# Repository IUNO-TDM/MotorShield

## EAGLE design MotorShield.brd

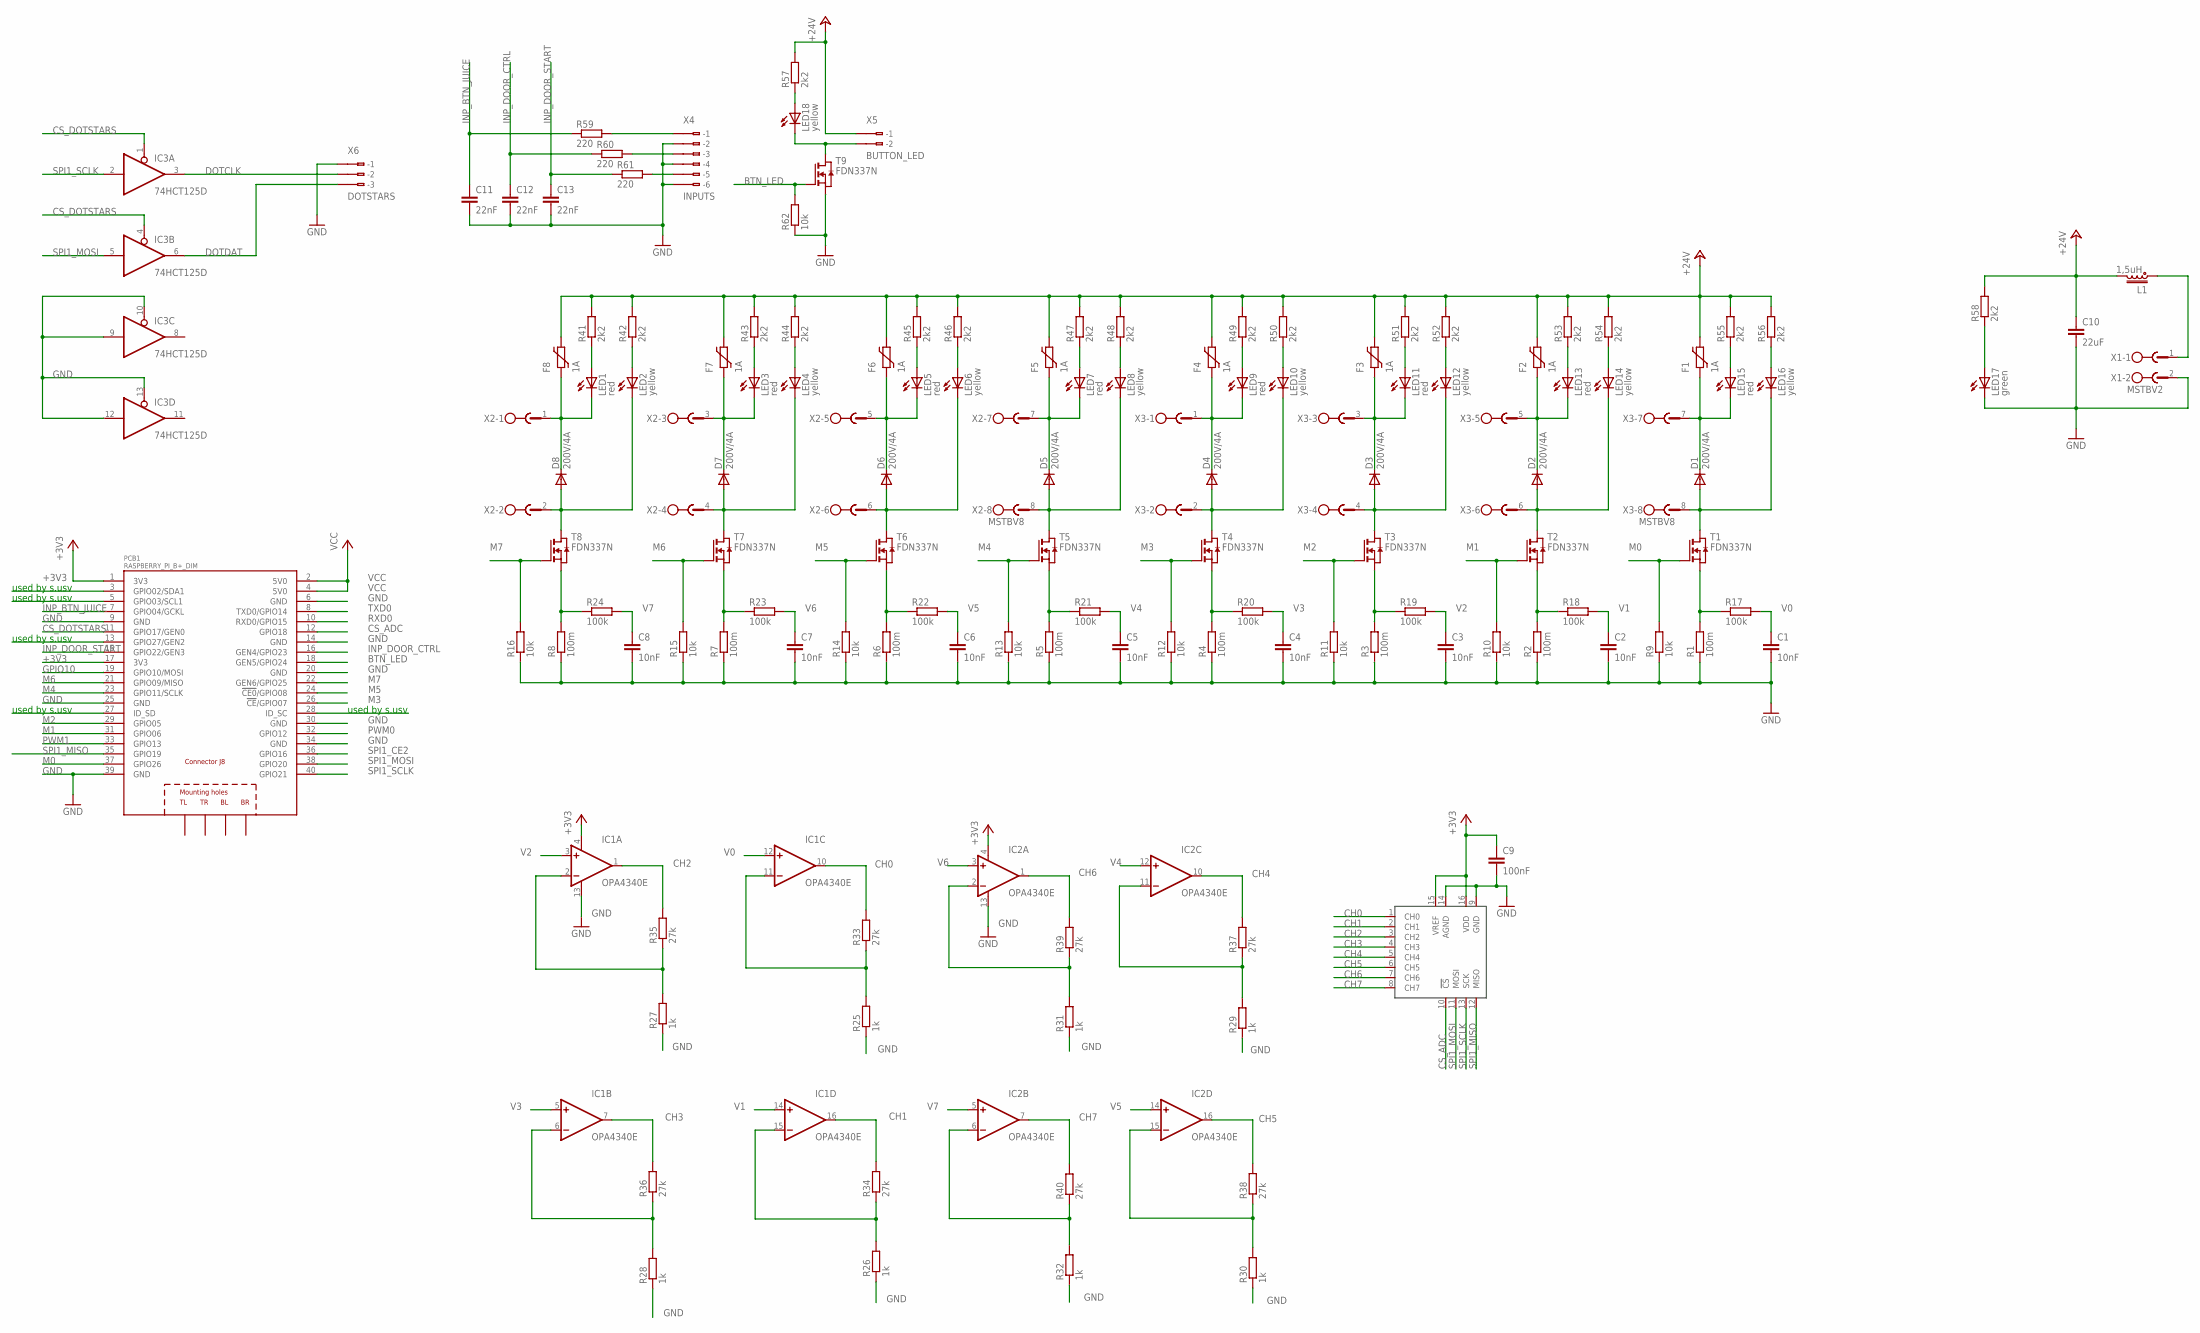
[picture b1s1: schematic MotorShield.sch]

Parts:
C1, C2, C3, C4, C5, C6, C7, C8: 10nF; C0805
C9: 100nF; C0805
C10: 22uF; C1812
C11, C12, C13: 22nF; C0805K
D1, D2, D3, D4, D5, D6, D7, D8: 200V/4A; DO214AA
F1, F2, F3, F4, F5, F6, F7, F8: 1A; 1812L
IC1, IC2: OPA4340E; SSOP16BU
IC3: 74HCT125D; SO14
IC4: MCP3008SL; SO16
L1: 1,5uH; MPI4040
LED1, LED3, LED5, LED7, LED9, LED11, LED13, LED15: red; CHIP-LED0805
LED2, LED4, LED6, LED8, LED10, LED12, LED14, LED16, LED18: yellow; CHIP-LED0805
LED17: green; CHIP-LED0805
PCB1: RASPBERRY_PI_B+_DIM; RASPBERRY_PI_BPLUS_DIM
R1, R2, R3, R4, R5, R6, R7, R8: 100m; R0805
R9, R10, R11, R12, R13, R14, R15, R16, R62: 10k; R0805
R17, R18, R19, R20, R21, R22, R23, R24: 100k; R0805
R25, R26, R27, R28, R29, R30, R31, R32: 1k; R0805
R33, R34, R35, R36, R37, R38, R39, R40: 27k; R0805
R41, R42, R43, R44, R45, R46, R47, R48, R49, R50, R51, R52, R53, R54, R55, R56, R57, R58: 2k2; R0805
R59, R60, R61: 220; R0805
T1, T2, T3, T4, T5, T6, T7, T8, T9: FDN337N; SOT-23
X1: MSTBV2
X2, X3: MSTBV8
X4: INPUTS; 233-506
X5: BUTTON_LED; 233-502
X6: DOTSTARS; 233-503

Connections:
+3V3: C9.1, IC1.4 (V+), IC2.4 (V+), IC4.15 (VREF), IC4.16 (VDD), PCB1.1 (3V3), PCB1.17 (3V3)
+24V: C10.1, F1.2, F2.2, F3.2, F4.2, F5.2, F6.2, F7.2, F8.2, L1.2, R41.2, R42.2, R43.2, R44.2, R45.2, R46.2, R47.2, R48.2, R49.2, R50.2, R51.2, R52.2, R53.2, R54.2, R55.2, R56.2, R57.2, R58.2, X5.B1 (B-1)
BTN_LED: PCB1.18 (GEN5/GPIO24), R62.2, T9.3 (G)
CH0: IC1.10 (OUT), IC4.1 (CH0), R33.2
CH1: IC1.16 (OUT), IC4.2 (CH1), R34.2
CH2: IC1.1 (OUT), IC4.3 (CH2), R35.2
CH3: IC1.7 (OUT), IC4.4 (CH3), R36.2
CH4: IC2.10 (OUT), IC4.5 (CH4), R37.2
CH5: IC2.16 (OUT), IC4.6 (CH5), R38.2
CH6: IC2.1 (OUT), IC4.7 (CH6), R39.2
CH7: IC2.7 (OUT), IC4.8 (CH7), R40.2
CS_ADC: IC4.10 (!CS), PCB1.12 (GPIO18)
CS_DOTSTARS: IC3.1 (OE), IC3.4 (OE), PCB1.11 (GPIO17/GEN0)
D8: D8.C, F8.1, LED1.C, X2.1
DOTCLK: IC3.3 (O), X6.B2 (B-2)
DOTDAT: IC3.6 (O), X6.B3 (B-3)
GND: C1.2, C2.2, C3.2, C4.2, C5.2, C6.2, C7.2, C8.2, C9.2, C10.2, C11.2, C12.2, C13.2, IC1.13 (V-), IC2.13 (V-), IC3.7 (GND), IC3.9 (I), IC3.10 (OE), IC3.12 (I), IC3.13 (OE), IC4.9 (GND), IC4.14 (AGND), LED17.C, PCB1.6 (GND), PCB1.9 (GND), PCB1.14 (GND), PCB1.20 (GND), PCB1.25 (GND), PCB1.30 (GND), PCB1.34 (GND), PCB1.39 (GND), R1.1, R2.1, R3.1, R4.1, R5.1, R6.1, R7.1, R8.1, R9.1, R10.1, R11.1, R12.1, R13.1, R14.1, R15.1, R16.1, R25.1, R26.1, R27.1, R28.1, R29.1, R30.1, R31.1, R32.1, R62.1, T9.2 (S), X1.2, X4.B2 (B-2), X4.B4 (B-4), X4.B6 (B-6), X6.B1 (B-1)
GPIO10: PCB1.19 (GPIO10/MOSI)
GPIO27: PCB1.13 (GPIO27/GEN2)
INP_BTN_JUICE: C11.1, PCB1.7 (GPIO04/GCKL), R59.1
INP_DOOR_CTRL: C12.1, PCB1.16 (GEN4/GPIO23), R60.1
INP_DOOR_START: C13.1, PCB1.15 (GPIO22/GEN3), R61.1
M0: PCB1.37 (GPIO26), R9.2, T1.3 (G)
M1: PCB1.31 (GPIO06), R10.2, T2.3 (G)
M2: PCB1.29 (GPIO05), R11.2, T3.3 (G)
M3: PCB1.26 (!CE!/GPIO07), R12.2, T4.3 (G)
M4: PCB1.23 (GPIO11/SCLK), R13.2, T5.3 (G)
M5: PCB1.24 (!CE0!/GPIO08), R14.2, T6.3 (G)
M6: PCB1.21 (GPIO09/MISO), R15.2, T7.3 (G)
M7: PCB1.22 (GEN6/GPIO25), R16.2, T8.3 (G)
unnamed: D8.A, LED2.C, T8.1 (D), X2.2
unnamed: R8.2, R24.1, T8.2 (S)
unnamed: D1.C, F1.1, LED15.C, X3.7
unnamed: D2.C, F2.1, LED13.C, X3.5
unnamed: IC1.2 (-IN), R27.2, R35.1
unnamed: D3.C, F3.1, LED11.C, X3.3
unnamed: D4.C, F4.1, LED9.C, X3.1
unnamed: D5.C, F5.1, LED7.C, X2.7
unnamed: D7.A, LED4.C, T7.1 (D), X2.4
unnamed: R7.2, R23.1, T7.2 (S)
unnamed: D6.C, F6.1, LED5.C, X2.5
unnamed: D7.C, F7.1, LED3.C, X2.3
unnamed: IC1.6 (-IN), R28.2, R36.1
unnamed: D6.A, LED6.C, T6.1 (D), X2.6
unnamed: R6.2, R22.1, T6.2 (S)
unnamed: IC1.11 (-IN), R25.2, R33.1
unnamed: L1.1, X1.1
unnamed: LED15.A, R55.1
unnamed: LED16.A, R56.1
unnamed: D5.A, LED8.C, T5.1 (D), X2.8
unnamed: IC1.15 (-IN), R26.2, R34.1
unnamed: LED1.A, R41.1
unnamed: R5.2, R21.1, T5.2 (S)
unnamed: LED2.A, R42.1
unnamed: IC2.2 (-IN), R31.2, R39.1
unnamed: LED18.C, T9.1 (D), X5.B2 (B-2)
unnamed: R59.2, X4.B1 (B-1)
unnamed: IC2.6 (-IN), R32.2, R40.1
unnamed: LED3.A, R43.1
unnamed: LED4.A, R44.1
unnamed: IC2.11 (-IN), R29.2, R37.1
unnamed: D4.A, LED10.C, T4.1 (D), X3.2
unnamed: R4.2, R20.1, T4.2 (S)
unnamed: IC2.15 (-IN), R30.2, R38.1
unnamed: LED6.A, R46.1
unnamed: LED5.A, R45.1
unnamed: LED7.A, R47.1
unnamed: LED8.A, R48.1
unnamed: D3.A, LED12.C, T3.1 (D), X3.4
unnamed: R3.2, R19.1, T3.2 (S)
unnamed: LED9.A, R49.1
unnamed: LED10.A, R50.1
unnamed: LED11.A, R51.1
unnamed: LED12.A, R52.1
unnamed: D2.A, LED14.C, T2.1 (D), X3.6
unnamed: R2.2, R18.1, T2.2 (S)
unnamed: LED13.A, R53.1
unnamed: LED14.A, R54.1
unnamed: D1.A, LED16.C, T1.1 (D), X3.8
unnamed: R1.2, R17.1, T1.2 (S)
unnamed: R60.2, X4.B3 (B-3)
unnamed: R61.2, X4.B5 (B-5)
unnamed: LED17.A, R58.1
unnamed: LED18.A, R57.1
PWM0: PCB1.32 (GPIO12)
PWM1: PCB1.33 (GPIO13)
RXD0: PCB1.10 (RXD0/GPIO15)
SPI1_CE2: PCB1.36 (GPIO16)
SPI1_MISO: IC4.12 (MISO), PCB1.35 (GPIO19)
SPI1_MOSI: IC3.5 (I), IC4.11 (MOSI), PCB1.38 (GPIO20)
SPI1_SCLK: IC3.2 (I), IC4.13 (SCK), PCB1.40 (GPIO21)
TXD0: PCB1.8 (TXD0/GPIO14)
V0: C1.1, IC1.12 (+IN), R17.2
V1: C2.1, IC1.14 (+IN), R18.2
V2: C3.1, IC1.3 (+IN), R19.2
V3: C4.1, IC1.5 (+IN), R20.2
V4: C5.1, IC2.12 (+IN), R21.2
V5: C6.1, IC2.14 (+IN), R22.2
V6: C7.1, IC2.3 (+IN), R23.2
V7: C8.1, IC2.5 (+IN), R24.2
VCC: IC3.14 (VCC), PCB1.2 (5V0), PCB1.4 (5V0)

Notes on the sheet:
used by s.usv

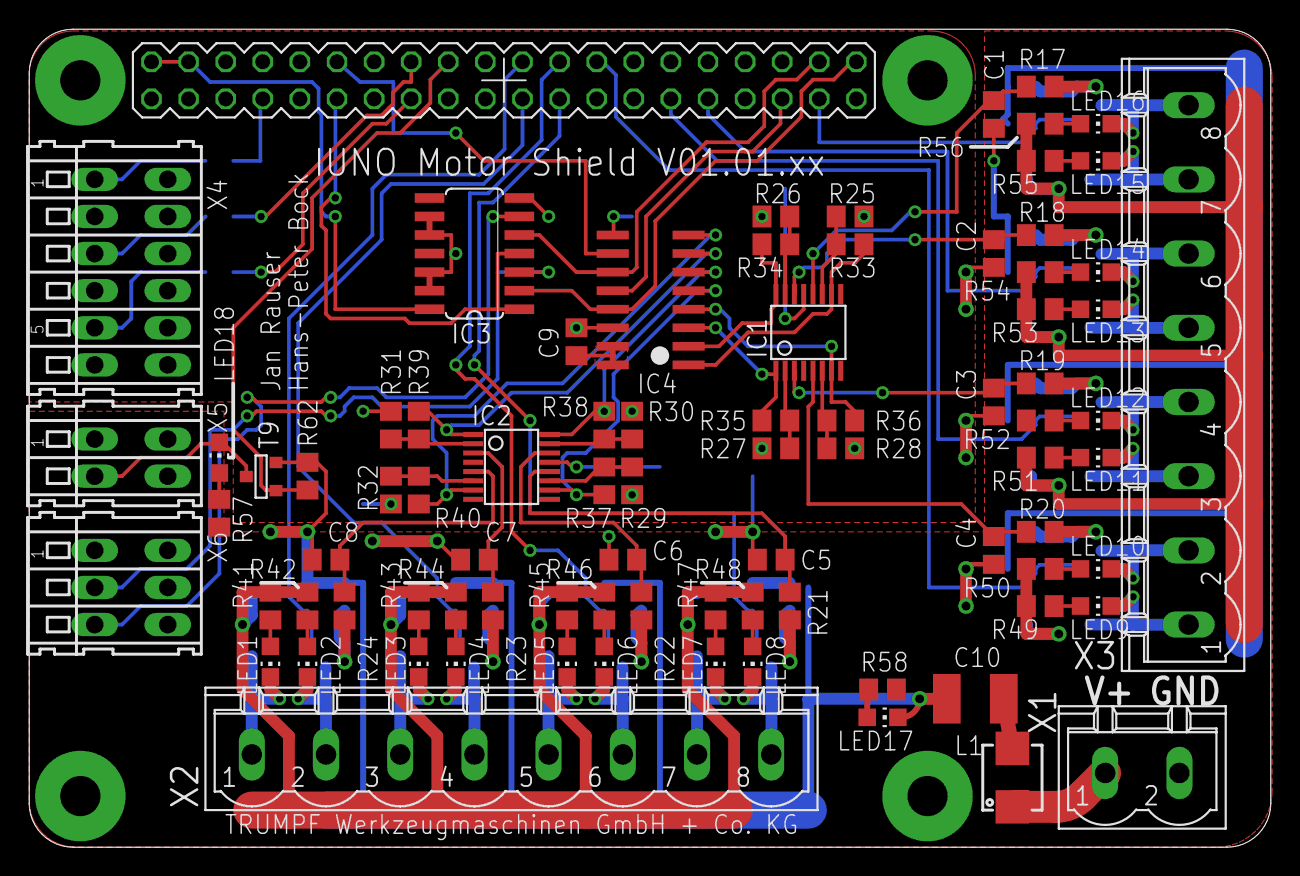
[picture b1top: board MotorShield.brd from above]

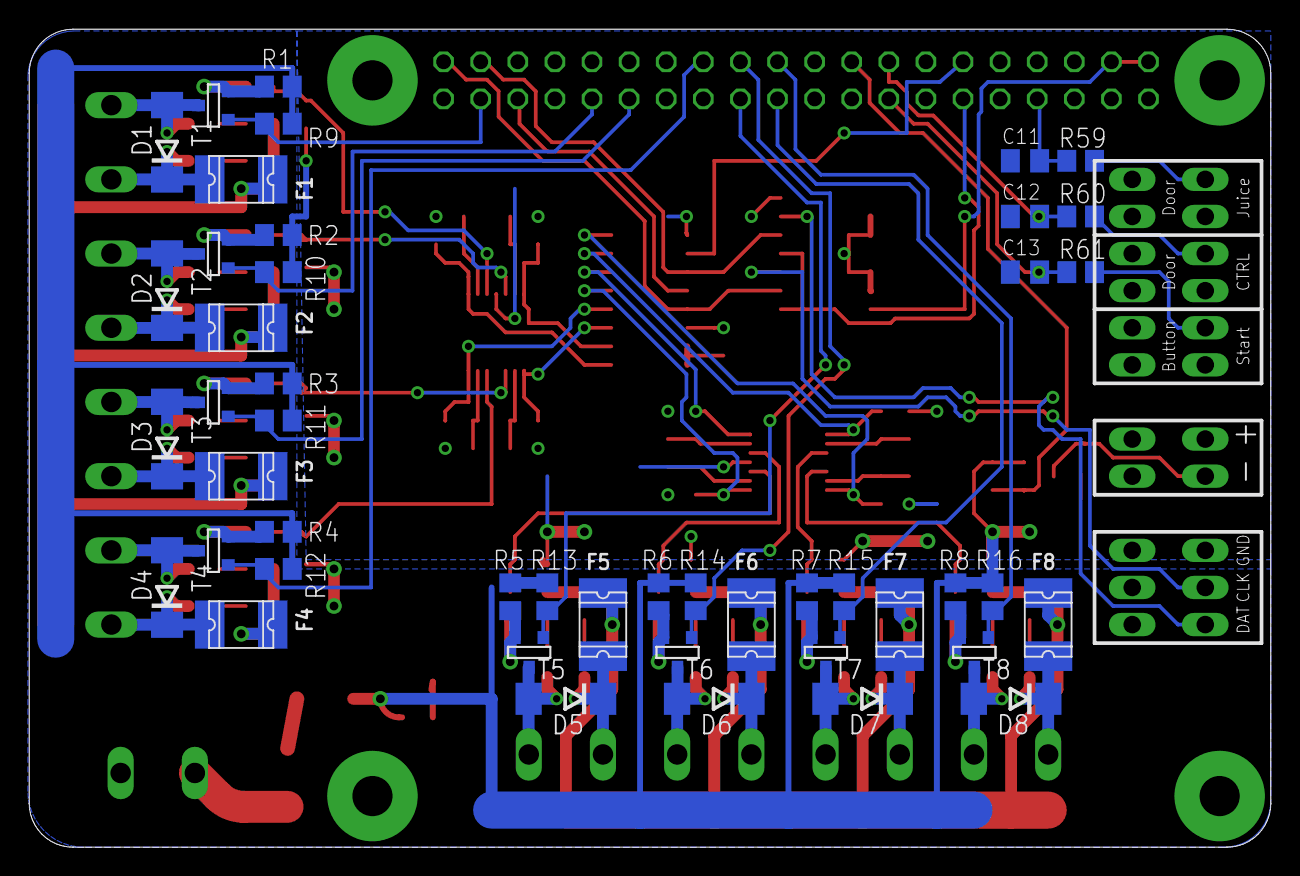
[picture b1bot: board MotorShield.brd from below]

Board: 2 copper layers, 85.0 x 56.0 mm, 130 parts (46 on the bottom side), 94 nets.

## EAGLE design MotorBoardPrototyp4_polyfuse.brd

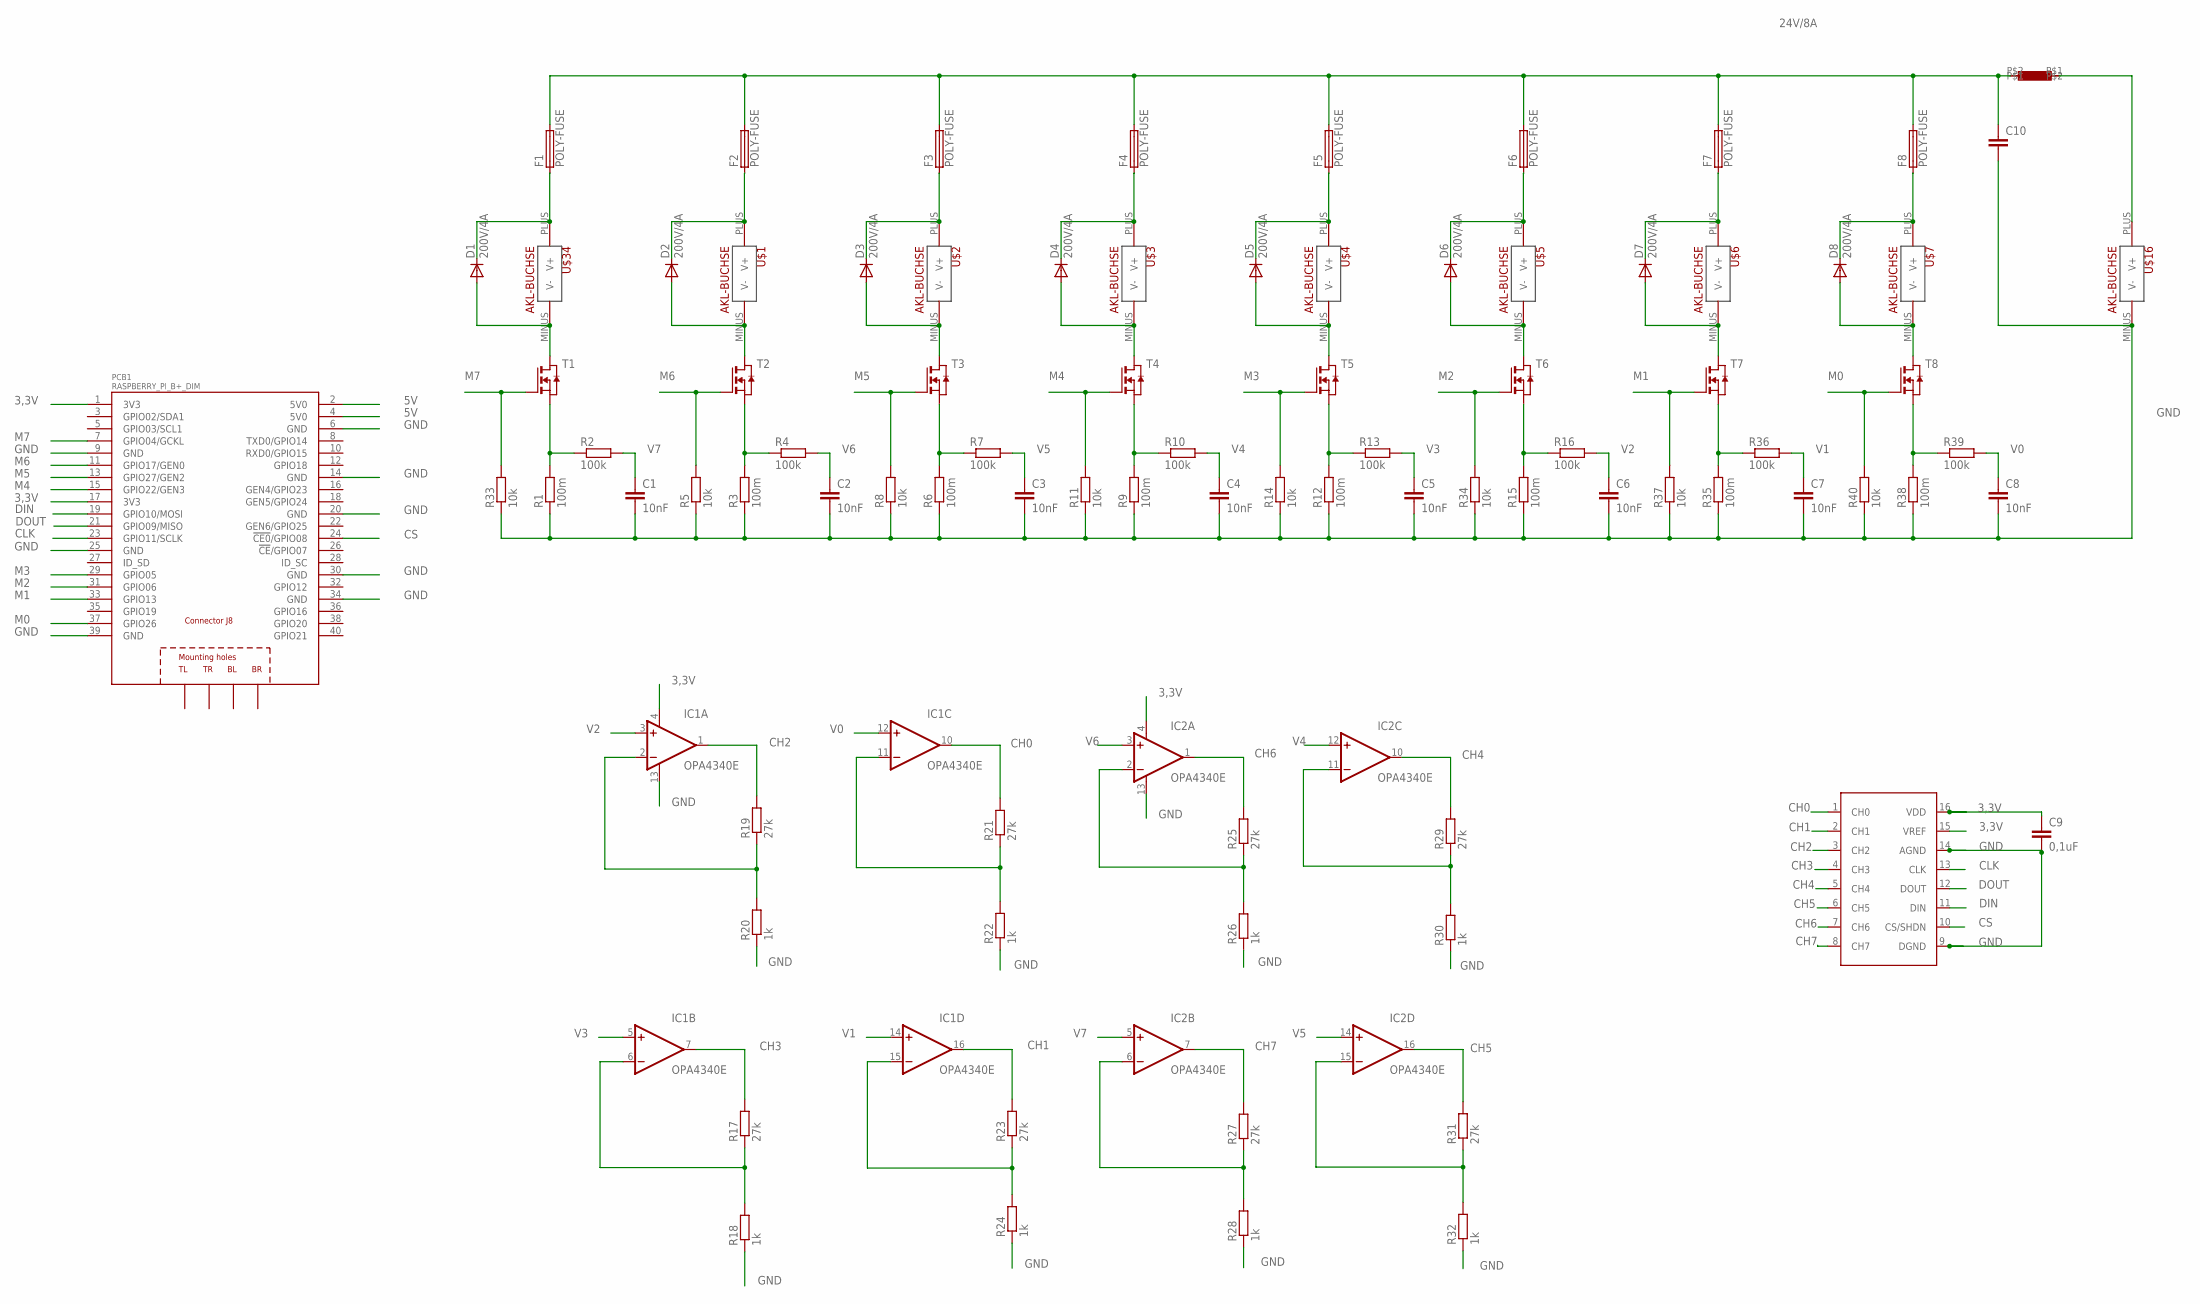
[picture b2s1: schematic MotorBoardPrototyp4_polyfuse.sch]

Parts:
C1, C2, C3, C4, C5, C6, C7, C8: 10nF; C0805
C9: 0,1uF; C0805
C10: C-EUC1812; C1812
D1, D2, D3, D4, D5, D6, D7, D8: 200V/4A; DO214AA
F1, F2, F3, F4, F5, F6, F7, F8: POLY-FUSE; 1812L050
IC1, IC2: OPA4340E; SSOP16BU
L1: MPI4040; 4040
PCB1: RASPBERRY_PI_B+_DIM; RASPBERRY_PI_BPLUS_DIM
R1, R3, R6, R9, R12, R15, R35, R38: 100m; R0805
R2, R4, R7, R10, R13, R16, R36, R39: 100k; R0805
R5, R8, R11, R14, R33, R34, R37, R40: 10k; R0805
R17, R19, R21, R23, R25, R27, R29, R31: 27k; R0805
R18, R20, R22, R24, R26, R28, R30, R32: 1k; R0805
T1, T2, T3, T4, T5, T6, T7, T8: NMOSSOT23; SOT-23
U$1, U$2, U$3, U$4, U$5, U$6, U$7, U$16, U$34: AKL-BUCHSE
U$58: MCP3008SO16; SO16

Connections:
3,3V: C9.1, IC1.4 (V+), IC2.4 (V+), PCB1.1 (3V3), PCB1.17 (3V3), U$58.15 (VREF), U$58.16 (VDD)
5V: PCB1.2 (5V0), PCB1.4 (5V0)
24V/1A: D1.C, F1.P$1 (1), U$34.PLUS (V+)
24V/8A: C10.1, F1.P$2 (2), F2.P$2 (2), F3.P$2 (2), F4.P$2 (2), F5.P$2 (2), F6.P$2 (2), F7.P$2 (2), F8.P$2 (2), L1.P$2
CH0: IC1.10 (OUT), R21.2, U$58.1 (CH0)
CH1: IC1.16 (OUT), R23.2, U$58.2 (CH1)
CH2: IC1.1 (OUT), R19.2, U$58.3 (CH2)
CH3: IC1.7 (OUT), R17.2, U$58.4 (CH3)
CH4: IC2.10 (OUT), R29.2, U$58.5 (CH4)
CH5: IC2.16 (OUT), R31.2, U$58.6 (CH5)
CH6: IC2.1 (OUT), R25.2, U$58.7 (CH6)
CH7: IC2.7 (OUT), R27.2, U$58.8 (CH7)
CLK: PCB1.23 (GPIO11/SCLK), U$58.13 (CLK)
CS: PCB1.24 (!CE0!/GPIO08), U$58.10 (CS/SHDN)
DIN: PCB1.19 (GPIO10/MOSI), U$58.11 (DIN)
DOUT: PCB1.21 (GPIO09/MISO), U$58.12 (DOUT)
GND: C1.2, C2.2, C3.2, C4.2, C5.2, C6.2, C7.2, C8.2, C9.2, C10.2, IC1.13 (V-), IC2.13 (V-), PCB1.6 (GND), PCB1.9 (GND), PCB1.14 (GND), PCB1.20 (GND), PCB1.25 (GND), PCB1.30 (GND), PCB1.34 (GND), PCB1.39 (GND), R1.1, R3.1, R5.1, R6.1, R8.1, R9.1, R11.1, R12.1, R14.1, R15.1, R18.1, R20.1, R22.1, R24.1, R26.1, R28.1, R30.1, R32.1, R33.1, R34.1, R35.1, R37.1, R38.1, R40.1, U$16.MINUS (V-), U$58.9 (DGND), U$58.14 (AGND)
M0: PCB1.37 (GPIO26), R40.2, T8.3 (G)
M1: PCB1.33 (GPIO13), R37.2, T7.3 (G)
M2: PCB1.31 (GPIO06), R34.2, T6.3 (G)
M3: PCB1.29 (GPIO05), R14.2, T5.3 (G)
M4: PCB1.15 (GPIO22/GEN3), R11.2, T4.3 (G)
M5: PCB1.13 (GPIO27/GEN2), R8.2, T3.3 (G)
M6: PCB1.11 (GPIO17/GEN0), R5.2, T2.3 (G)
M7: PCB1.7 (GPIO04/GCKL), R33.2, T1.3 (G)
unnamed: D1.A, T1.1 (D), U$34.MINUS (V-)
unnamed: R1.2, R2.1, T1.2 (S)
unnamed: D8.C, F8.P$1 (1), U$7.PLUS (V+)
unnamed: D7.C, F7.P$1 (1), U$6.PLUS (V+)
unnamed: IC1.2 (-IN), R19.1, R20.2
unnamed: D6.C, F6.P$1 (1), U$5.PLUS (V+)
unnamed: D5.C, F5.P$1 (1), U$4.PLUS (V+)
unnamed: D4.C, F4.P$1 (1), U$3.PLUS (V+)
unnamed: D2.A, T2.1 (D), U$1.MINUS (V-)
unnamed: R3.2, R4.1, T2.2 (S)
unnamed: D3.C, F3.P$1 (1), U$2.PLUS (V+)
unnamed: D2.C, F2.P$1 (1), U$1.PLUS (V+)
unnamed: IC1.6 (-IN), R17.1, R18.2
unnamed: D3.A, T3.1 (D), U$2.MINUS (V-)
unnamed: R6.2, R7.1, T3.2 (S)
unnamed: IC1.11 (-IN), R21.1, R22.2
unnamed: D4.A, T4.1 (D), U$3.MINUS (V-)
unnamed: IC1.15 (-IN), R23.1, R24.2
unnamed: L1.P$1, U$16.PLUS (V+)
unnamed: R9.2, R10.1, T4.2 (S)
unnamed: IC2.2 (-IN), R25.1, R26.2
unnamed: IC2.6 (-IN), R27.1, R28.2
unnamed: IC2.11 (-IN), R29.1, R30.2
unnamed: D5.A, T5.1 (D), U$4.MINUS (V-)
unnamed: R12.2, R13.1, T5.2 (S)
unnamed: IC2.15 (-IN), R31.1, R32.2
unnamed: D6.A, T6.1 (D), U$5.MINUS (V-)
unnamed: R15.2, R16.1, T6.2 (S)
unnamed: D7.A, T7.1 (D), U$6.MINUS (V-)
unnamed: R35.2, R36.1, T7.2 (S)
unnamed: D8.A, T8.1 (D), U$7.MINUS (V-)
unnamed: R38.2, R39.1, T8.2 (S)
V0: C8.1, IC1.12 (+IN), R39.2
V1: C7.1, IC1.14 (+IN), R36.2
V2: C6.1, IC1.3 (+IN), R16.2
V3: C5.1, IC1.5 (+IN), R13.2
V4: C4.1, IC2.12 (+IN), R10.2
V5: C3.1, IC2.14 (+IN), R7.2
V6: C2.1, IC2.3 (+IN), R4.2
V7: C1.1, IC2.5 (+IN), R2.2

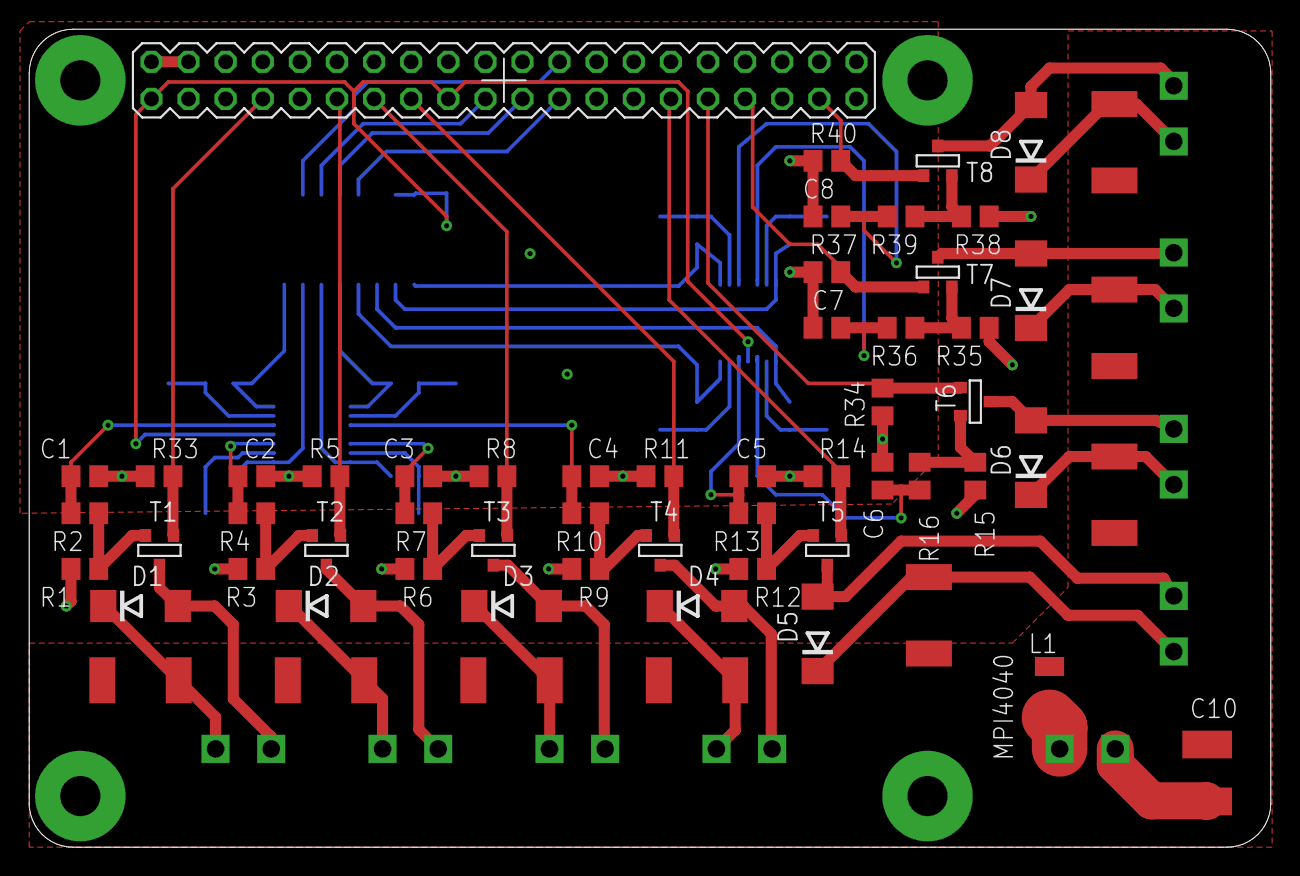
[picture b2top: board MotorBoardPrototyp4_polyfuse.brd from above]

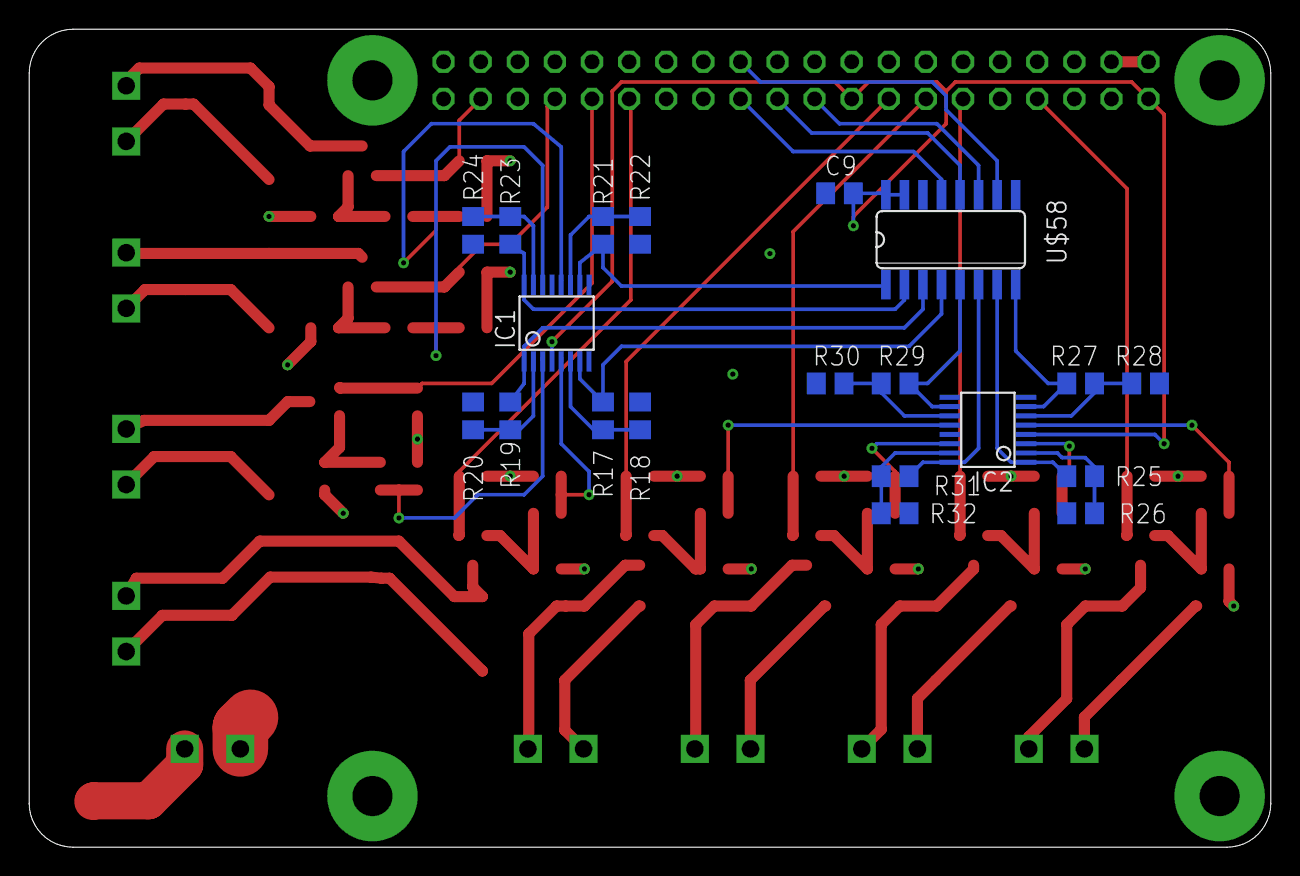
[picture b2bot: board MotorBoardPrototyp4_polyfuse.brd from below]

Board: 2 copper layers, 85.0 x 56.0 mm, 88 parts (20 on the bottom side), 65 nets.

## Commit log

2017-09-05 corrected MISO and MOSI closes #2
2017-09-05 removed ptc fuse versions
2017-09-05 corrected diameter of pads closes #1
2017-09-05 corrected diameter for pads closes #1
2017-09-05 added partlist
2017-09-05 renamed files
2017-09-05 converted file format back to eagle version 6.6.0
2017-10-09 marked gpios that are used by s.usv basic, see #10
2017-10-09 added 74HCT125D for DotStar pixels, see #3
2017-12-01 added label to power input closes #15
2017-12-01 pump no. 5 is now controlled by GPIO23 fixes #10
2017-12-01 changed connectors fixes #12
2017-12-01 added connectors for inputs, button LED and dotstars fixes #7
2017-12-01 changed fuse library to ptc-litlefuse from https://github.com/halfakop/eagle-lbr
2017-12-01 added LEDs to indicate powered outputs and tripped fuses fixes #4, fixes #6
2017-12-01 exchanged MCP3008 symbol and footprint https://github.com/hpbock/PCB-Designs/blob/master/!Libraries/MCP3008.lbr
2017-12-01 added net classes and tried to place components for M1
2017-12-07 assigned values to protective resistors
2017-12-07 added used libraries as submodules
2017-12-07 routed devices for M4 and M3
2017-12-07 routed M1 to M4
2017-12-07 placed parts for M5-M6
2017-12-10 routed op-amps
2017-12-12 more routing
2017-12-13 completely changed wiring of GPIOs https://github.com/IUNO-TDM/PumpControl/issues/27 https://github.com/IUNO-TDM/MotorShield/issues/11
2017-12-18 added power indicator led
2017-12-18 finished routing, no more airwires :)
2017-12-18 shrunk most vias
2017-12-19 revised routing
2017-12-19 placed names on top side
2017-12-19 placed names on bottom side
2017-12-21 Create LICENSE
    License file was missing
2017-12-22 optimized some routes
2018-01-07 minor changes to pcb
2018-01-08 added name and version number of shield to top silkscreen
2018-01-08 marked version label as development version
2018-01-09 changed wago clamps fixes #18
2018-01-15 CC BY SA
2018-01-16 moved apart overlapping circuits in schematic
2018-01-16 added button led reordered device names
2018-01-16 version V01.00.01
2018-01-16 marked as developement version
2018-01-22 optimized some wires and names
2018-01-30 fixed some badly misplaced resistor labels
2018-02-05 added markers to layer tName
2018-02-08 Moved input for start button near to X5. #24
2018-02-08 added connector labels to X4 #24
2018-02-08 added connector labels to X5 and X6 fixes #21, fixes #22
2018-02-08 debounced inputs fixes #20
2018-02-09 fixed footprint of L1 fixes #23
2018-02-14 moved C9 to top layer
